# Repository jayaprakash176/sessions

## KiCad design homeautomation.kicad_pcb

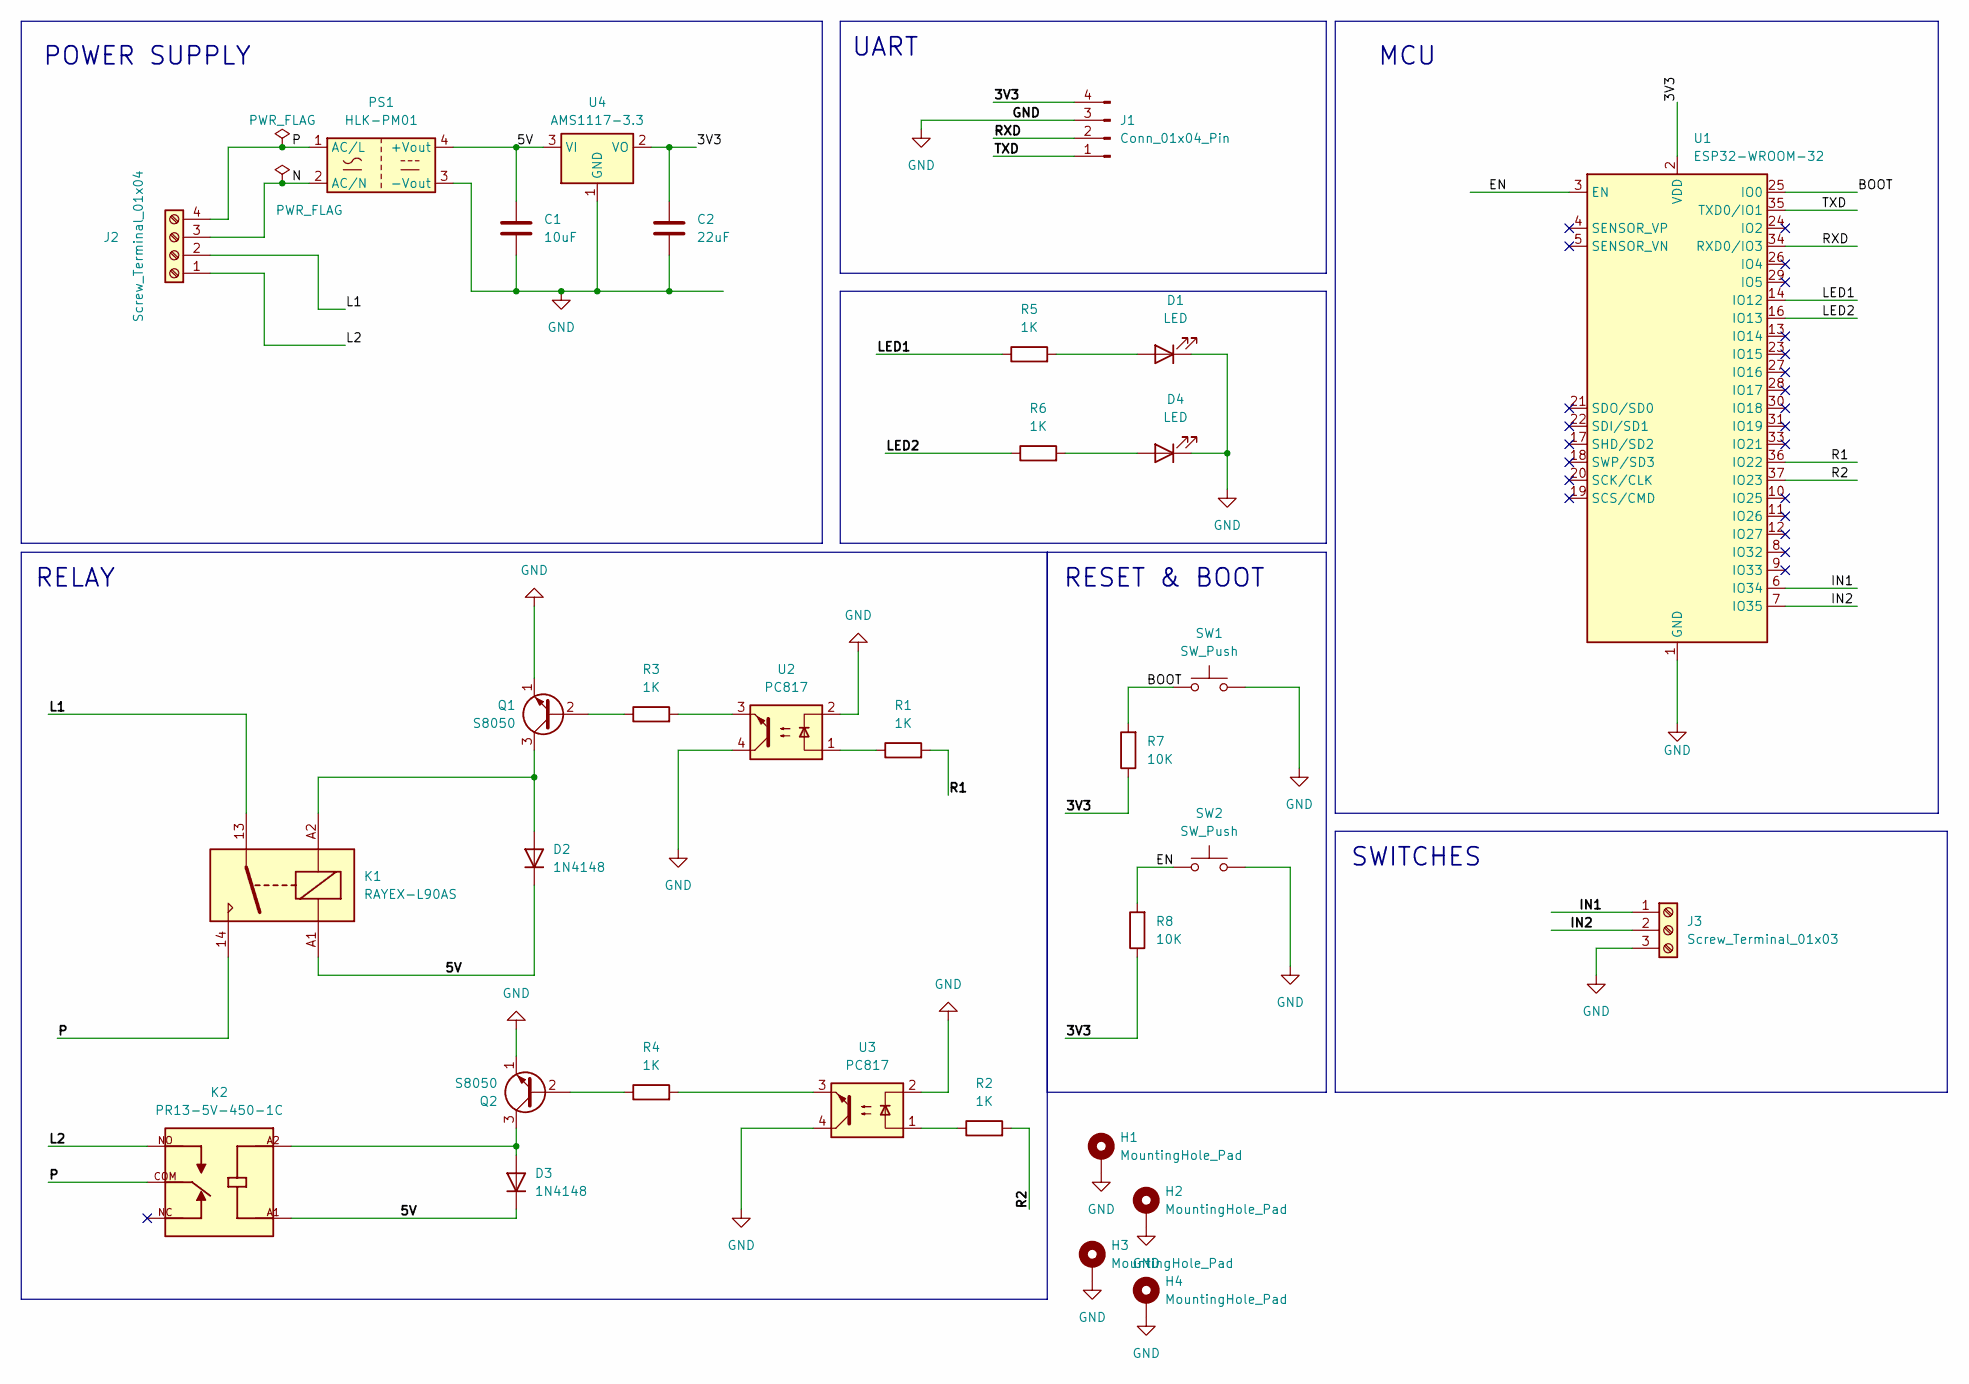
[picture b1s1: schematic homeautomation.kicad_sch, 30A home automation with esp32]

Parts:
C1: 10uF; C_0805_2012Metric
C2: 22uF; C_0805_2012Metric
D1, D4: LED; LED_0805_2012Metric
D2, D3: 1N4148; D_DO-35_SOD27_P7.62mm_Horizontal
H1, H2, H3, H4: MountingHole_Pad; MountingHole_2.7mm_M2.5_Pad_Via
J1: Conn_01x04_Pin; PinHeader_1x04_P2.54mm_Vertical
J2: Screw_Terminal_01x04; TerminalBlock_bornier-4_P5.08mm
J3: Screw_Terminal_01x03; TerminalBlock_bornier-3_P5.08mm
K1: RAYEX-L90AS; Relay_SPST_RAYEX-L90AS
K2: PR13-5V-450-1C; RELAY_PR13-5V-450-1C; PARTREV 1.0
PS1: HLK-PM01; Converter_ACDC_Hi-Link_HLK-PMxx
Q1, Q2: S8050; TO-92_Inline
R1, R2, R3, R4, R5, R6: 1K; R_0805_2012Metric
R7, R8: 10K; R_0805_2012Metric
SW1, SW2: SW_Push; SW_PUSH_6mm
U1: ESP32-WROOM-32
U2, U3: PC817; DIP-4_W7.62mm
U4: AMS1117-3.3; SOT-223-3_TabPin2

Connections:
/3V3: C2.1, J1.4, R7.1, R8.1, U1.2 (VDD), U4.2 (VO)
/5V: C1.1, D2.1 (K), D3.1 (K), K1.A1, K2.A1, PS1.4 (+Vout), U4.3 (VI)
/BOOT: R7.2, SW1.1, U1.25 (IO0)
/EN: R8.2, SW2.1, U1.3 (EN)
/IN1: J3.1, U1.6 (IO34)
/IN2: J3.2, U1.7 (IO35)
/L1: J2.2, K1.13
/L2: J2.1, K2.NO
/LED1: R5.1, U1.14 (IO12)
/LED2: R6.1, U1.16 (IO13)
/N: J2.3, PS1.2 (AC/N)
/P: J2.4, K1.14, K2.COM, PS1.1 (AC/L)
/R1: R1.2, U1.36 (IO22)
/R2: R2.2, U1.37 (IO23)
/RXD: J1.2, U1.34 (RXD0/IO3)
/TXD: J1.1, U1.35 (TXD0/IO1)
GND: C1.2, C2.2, D1.1 (K), D4.1 (K), H1.1, H2.1, H3.1, H4.1, J1.3, J3.3, PS1.3 (-Vout), Q1.1 (E), Q2.1 (E), SW1.2, SW2.2, U1.1 (GND), U1.15 (GND), U1.38 (GND), U1.39 (GND), U2.2, U2.4, U3.2, U3.4, U4.1 (GND)
unnamed: D1.2 (A), R5.2
unnamed: D2.2 (A), K1.A2, Q1.3 (C)
unnamed: D3.2 (A), K2.A2, Q2.3 (C)
unnamed: D4.2 (A), R6.2
unnamed: Q1.2 (B), R3.1
unnamed: Q2.2 (B), R4.1
unnamed: R1.1, U2.1
unnamed: R2.1, U3.1
unnamed: R3.2, U2.3
unnamed: R4.2, U3.3

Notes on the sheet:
MCU
RESET & BOOT
UART
POWER SUPPLY
SWITCHES
RELAY

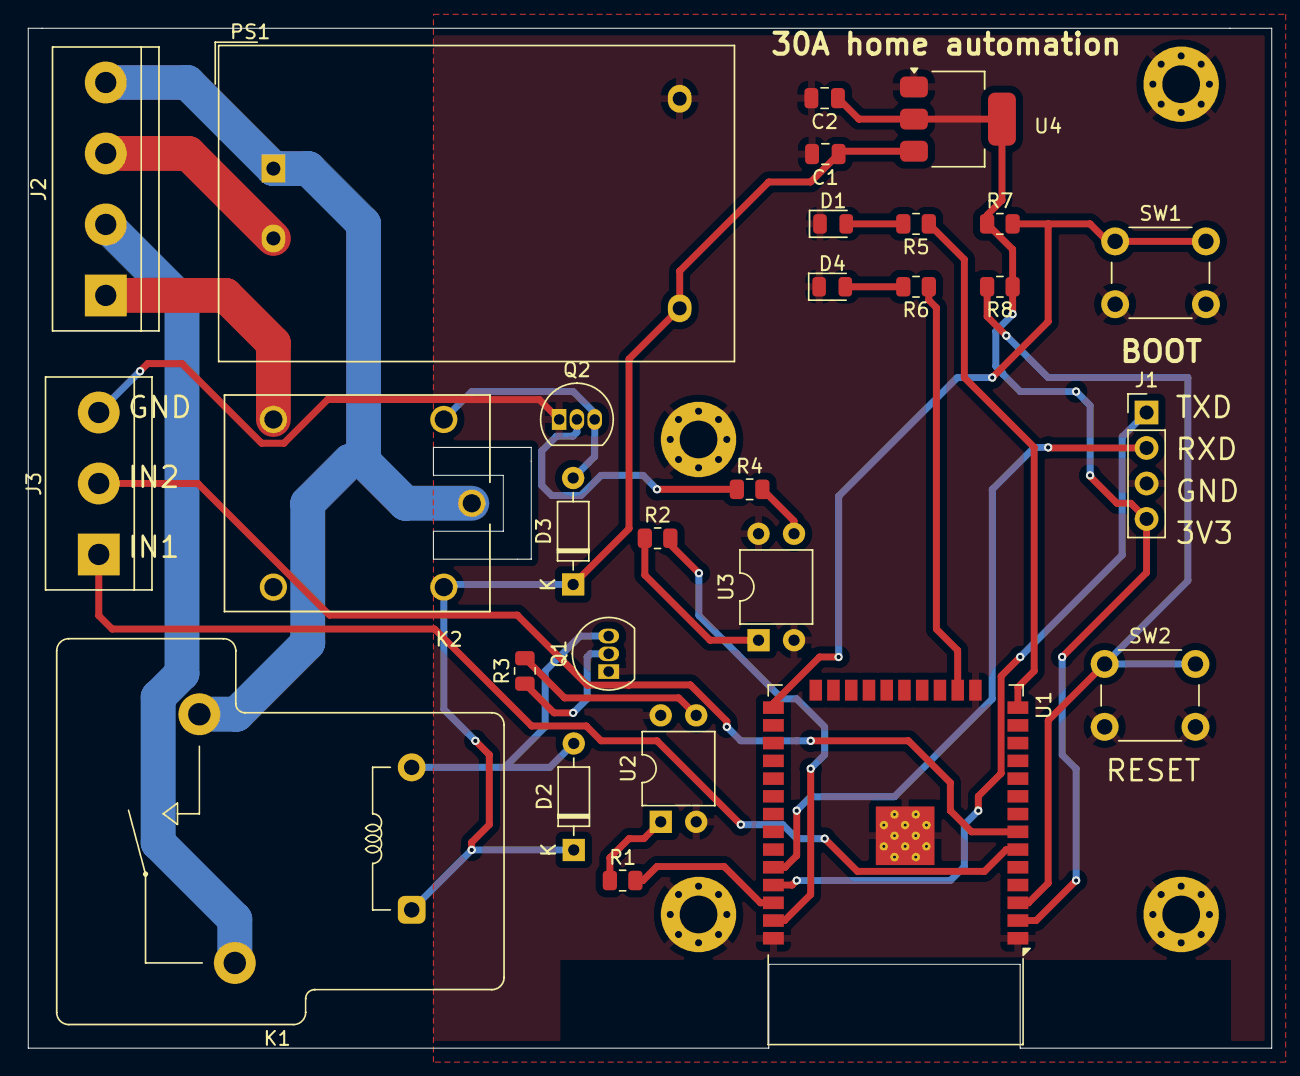
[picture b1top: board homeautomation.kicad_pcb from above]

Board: 2 copper layers, 89.0 x 73.0 mm, 32 parts (0 on the bottom side), 27 nets.
